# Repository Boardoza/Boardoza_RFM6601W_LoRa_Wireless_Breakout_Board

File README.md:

# Boardoza RFM6601W LoRa Wireless Communication Module Breakout Board

The **Boardoza RFM6601W** is a LoRa wireless communication module designed by **HOPERF**, featuring an integrated LoRa transceiver, RF transmitter/receiver, and a powerful **32-bit ARM Cortex-M4 RISC microcontroller** operating at 48 MHz. This module is ideal for long-range, low-power wireless applications including IoT sensor networks, smart agriculture, industrial monitoring, and remote telemetry systems.

The module operates with **3.3V or 5V** supply voltage and communicates via **UART** interface, making it compatible with a wide range of microcontroller platforms. It supports operating frequencies  **868 MHz** with exceptional receiving sensitivity of **-138 dBm** at maximum spreading factor.

## [Click here to purchase!](https://www.ozdisan.com/p/arduino-sensorleri-ve-modulleri-613/boardoza-boardoza-rfm6601w-1202716)

|Front Side|Back Side|
|:---:|:---:|
| | |

---

## Key Features

- **Integrated MCU:** 32-bit ARM Cortex-M4 processor at 48 MHz.  
- **Operation Frequency Range:** 868 MHz ISM bands.
- **High Sensitivity:** –138 dBm at SF=12, BW=125 kHz.  
- **Adjustable Output Power:** Up to +2 dBm.  
- **Low Power Consumption:** 10 mA RX, 20 mA TX at +2 dBm.  
- **Simple UART Interface:** Easy integration with most microcontrollers.  
- **Dual Voltage Support:** Operates at 3.3V or 5V.  
- **Compact Form Factor:** Ideal for wireless embedded applications.  

---

## Technical Specifications

**Manufacturer:** HOPERF  
**Model:** RFM6601W  
**Input Voltage:** 3.3V - 5V  
**Voltage Input Type:** 7-pin 2.50mm header  
**Interface:** UART  
**Functions:** LoRa Wireless Communication Module  
**Processor:** ARM Cortex-M4 32-bit RISC MCU  
**Clock Speed:** 48 MHz  
**Frequency Range:** 868 MHz - 868.2 MHz (continuous coverage)  
**Operating Frequencies:**  868 MHz  
**Receiving Sensitivity:** -138 dBm @SF=12, BW=125KHz  
**Transmit Current:** 20 mA @+2dBm, 868MHz  
**Receive Current:** 10 mA @868.1MHz  
**Operating Temperature:** -40°C ~ +85°C  
**Board Dimensions:** 40mm x 40mm

---

## Board Pinout

### **( J1 ) Main Communication & Power Pins**

| Pin Number | Pin Name | Description |
|:---:|:---:|---|
| 1 | GND | Ground |
| 2 | TX | MCU GPIO (UART_RXD) |
| 3 | RX | MCU GPIO (UART_TXD) |
| 4 | CLOCK | SWD CLK (Serial Wire Debug Clock) |
| 5 | DATA | SWD DATA (Serial Wire Debug Data) |
| 6 | RESET | Reset signal (active low) |
| 7 | VDD | Power supply input (3.3V - 5V) |

### **( J2 ) GPIO Extension Pins**

| Pin Number | Pin Name | Description |
|:---:|:---:|---|
| 1 | GPIO32 | MCU General Purpose I/O |
| 2 | GPIO33 | MCU General Purpose I/O |
| 3 | GPIO37 | MCU General Purpose I/O |
| 4 | GPIO1 | MCU General Purpose I/O |
| 5 | GPIO0 | MCU General Purpose I/O |
| 6 | GPIO03 | MCU General Purpose I/O |
| 7 | GPIO02 | MCU General Purpose I/O |
| 8 | GPIO16 | MCU General Purpose I/O |
| 9 | GPIO14 | MCU General Purpose I/O |
| 10 | GPIO15 | MCU General Purpose I/O |

### **( J3 ) GPIO Extension Pins**

| Pin Number | Pin Name | Description |
|:---:|:---:|---|
| 1 | GPIO44 | MCU General Purpose I/O |
| 2 | GPIO45 | MCU General Purpose I/O |
| 3 | GPIO47 | MCU General Purpose I/O |
| 4 | GPIO09 | MCU General Purpose I/O |
| 5 | GPIO04 | MCU General Purpose I/O |
| 6 | GPIO05 | MCU General Purpose I/O |
| 7 | GPIO08 | MCU General Purpose I/O |
| 8 | GPIO11 | MCU General Purpose I/O |
| 9 | GPIO58 | MCU General Purpose I/O |
| 10 | GPIO60 | MCU General Purpose I/O |

---

## Board Dimensions

---

## Compatible Antennas

For reliable and long-range RF performance in the **868 MHz ISM band**, it is strongly recommended to use a properly tuned **50Ω external antenna** specifically designed for 868 MHz operation. A matched antenna improves transmission efficiency, enhances receiver sensitivity, and ensures stable communication performance.

Using an antenna optimized for the operating frequency helps minimize return loss, low VSWR (Voltage Standing Wave Ratio) and maximizes RF power transfer from the module.

[Recommended Antenna: 868 MHz 3 dBi Omni-Directional LoRa SMA Antenna](https://www.ozdisan.com/p/rf-antenler-660/sunnyway-rf-swf022-sw24008ib77-1210812)

**Key Antenna Characteristics:**

- **Frequency:** 868 MHz ISM Band  
- **Gain:** 3.62 dBi  
- **Radiation Pattern:** Omni-directional  
- **Connector Type:** IPEX MHF1  
- **Impedance:** 50Ω  

>  **Important:** Always connect the antenna before powering the RF module. Operating the module without a connected antenna may cause RF stage damage and significantly reduce transmission performance.

---

## Step Files

[Boardoza RFM6601W.step](./assets/RFM6601W%20Step.step)

---

## Datasheet

[HOPERF RFM6601W Datasheet.pdf](./assets/RFM6601W%20Datasheet.pdf)

---

## Version History

- V1.0.0 - Initial Release

---

## Support

- If you have any questions or need support, please contact <support@boardoza.com>

---

## License

Shield: [![CC BY-SA 4.0][cc-by-sa-shield]][cc-by-sa]

This work is licensed under a [Creative Commons Attribution-ShareAlike 4.0 International License][cc-by-sa].

[![CC BY-SA 4.0][cc-by-sa-image]][cc-by-sa]

[cc-by-sa]: http://creativecommons.org/licenses/by-sa/4.0/
[cc-by-sa-image]: https://licensebuttons.net/l/by-sa/4.0/88x31.png
[cc-by-sa-shield]: https://img.shields.io/badge/License-CC%20BY--SA%204.0-lightgrey.svg

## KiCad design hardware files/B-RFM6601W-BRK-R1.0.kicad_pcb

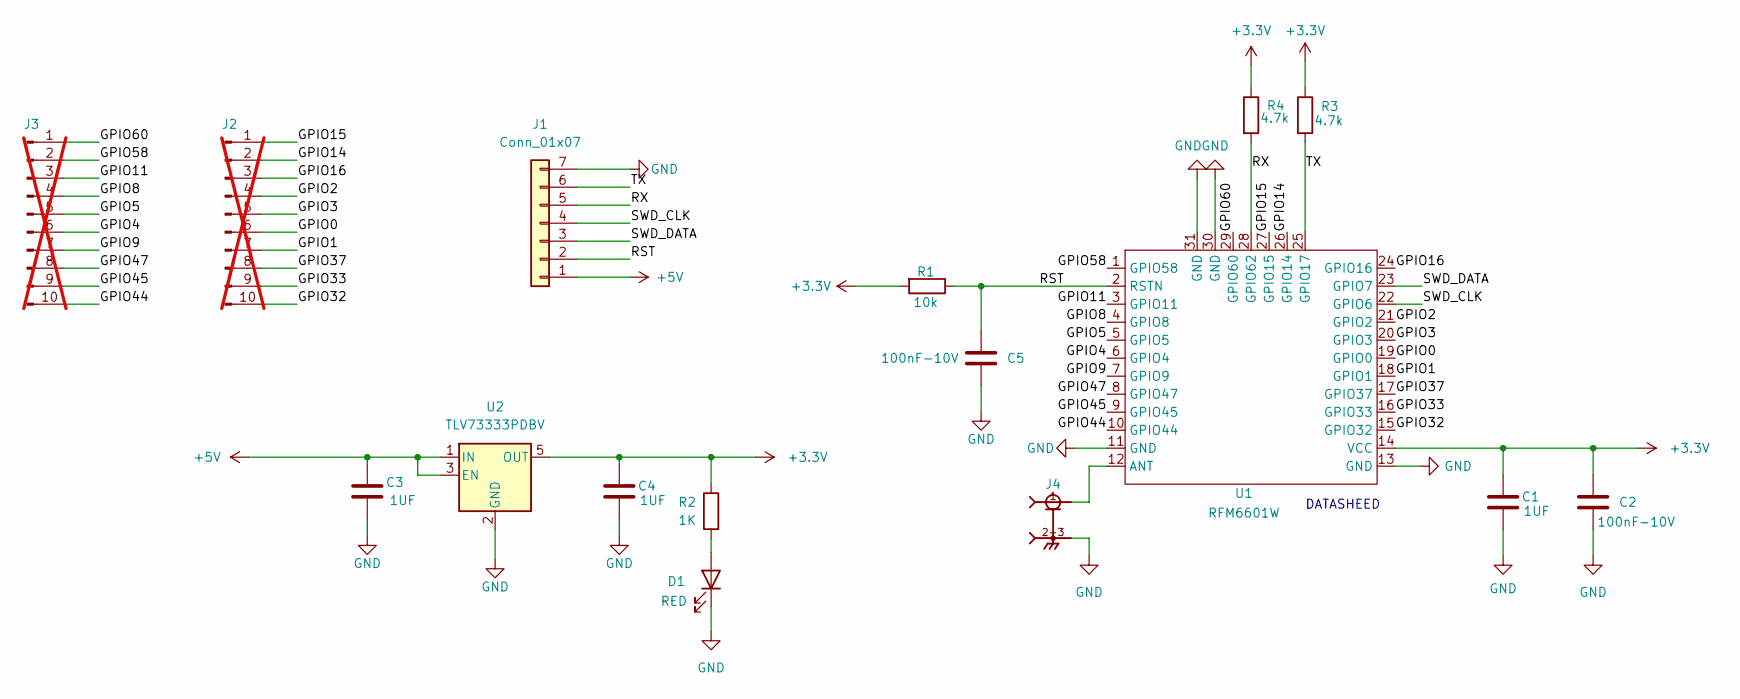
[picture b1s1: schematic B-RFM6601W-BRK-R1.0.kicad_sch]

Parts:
C1, C3, C4: 1UF; C_0603_1608Metric; MPN CL10A105KO8NNNC
C2, C5: 100nF-10V; C_0603_1608Metric; MPN CL10B104KO8NNNC
D1: RED; LED_0603_1608Metric; MPN LTST-C190KRKT
J1: Conn_01x07; 2317-07S_1x07_P2.50mm_Vertical; MPN L-KLS1-2.50-07-S
J2, J3: Conn_01x10_Pin; PinHeader_1x10_P2.54mm_Vertical; not fitted
J4: U.FL-R-SMT_10_; HRS_U.FL-R-SMT_10_; MPN L-KLS1-IPEX-20279-001E-0
R1: 10k; R_0603_1608Metric; MPN RC0603JR-0710KL
R2: 1K; R_0603_1608Metric; MPN RC0603JR-071KL
R3, R4: 4.7k; R_0603_1608Metric; MPN 2.485.430
U1: RFM6601W; MPN RFM6601W-868S2
U2: TLV73333PDBV; SOT-23-5; MPN TLV73333PDBVR

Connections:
+3.3V: C1.1, C2.1, C4.1, R1.2, R2.1, R3.1, R4.1, U1.14 (VCC), U2.5 (OUT)
+5V: C3.1, J1.1, U2.1 (IN), U2.3 (EN)
/GPIO0: J2.6, U1.19 (GPIO0)
/GPIO1: J2.7, U1.18 (GPIO1)
/GPIO2: J2.4, U1.21 (GPIO2)
/GPIO3: J2.5, U1.20 (GPIO3)
/GPIO4: J3.6, U1.6 (GPIO4)
/GPIO5: J3.5, U1.5 (GPIO5)
/GPIO8: J3.4, U1.4 (GPIO8)
/GPIO9: J3.7, U1.7 (GPIO9)
/GPIO11: J3.3, U1.3 (GPIO11)
/GPIO14: J2.2, U1.26 (GPIO14)
/GPIO15: J2.1, U1.27 (GPIO15)
/GPIO16: J2.3, U1.24 (GPIO16)
/GPIO32: J2.10, U1.15 (GPIO32)
/GPIO33: J2.9, U1.16 (GPIO33)
/GPIO37: J2.8, U1.17 (GPIO37)
/GPIO44: J3.10, U1.10 (GPIO44)
/GPIO45: J3.9, U1.9 (GPIO45)
/GPIO47: J3.8, U1.8 (GPIO47)
/GPIO58: J3.2, U1.1 (GPIO58)
/GPIO60: J3.1, U1.29 (GPIO60)
/RST: C5.1, J1.2, R1.1, U1.2 (RSTN)
/RX: J1.5, R4.2, U1.28 (GPIO62)
/SWD_CLK: J1.4, U1.22 (GPIO6)
/SWD_DATA: J1.3, U1.23 (GPIO7)
/TX: J1.6, R3.2, U1.25 (GPIO17)
GND: C1.2, C2.2, C3.2, C4.2, C5.2, D1.1 (K), J1.7, J4., J4.2, J4.2-3, J4.3, U1.11 (GND), U1.13 (GND), U1.30 (GND), U1.31 (GND), U2.2 (GND)
unnamed: D1.2 (A), R2.2
unnamed: J4.1, U1.12 (ANT)

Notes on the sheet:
DATASHEED

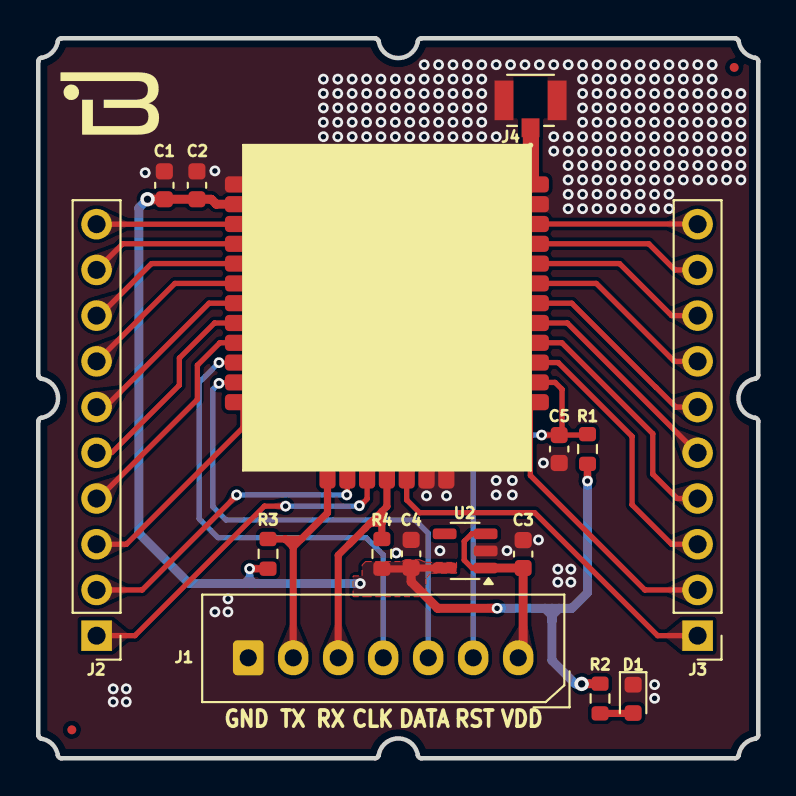
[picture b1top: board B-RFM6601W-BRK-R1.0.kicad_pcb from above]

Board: 2 copper layers, 40.0 x 40.0 mm, 16 parts (0 on the bottom side), 30 nets.

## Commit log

2025-11-17 Add RFM6601W example
2026-02-17 Update README.md
    Add Compatible Antennas
2026-04-29 Fix library structure
